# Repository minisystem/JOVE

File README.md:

SYSTEM80 JOVE Multimode Filter
============

Roland Jupiter 6 inspired multimode filter in 14HP Eurorack format. IR3109s replaced with LM13700 OTAs.
Selectable 24 dB low pass, bonus 2 pole 12 dB low pass, band pass and high pass modes.

Product page: http://system80.net/product/jove/<br>

Demos:<br>
https://soundcloud.com/system_80/sets/jove-demo<br>
https://soundcloud.com/system_80/sets/jove-mimoid-demo<br>
https://www.youtube.com/watch?v=VFNtQRDSUw4

EDA files generated in KiCad 4.0.2. Schematic library here: https://github.com/minisystem/MyKicadLibraries/blob/master/MySynthParts.lib
KiCad GitHub libraries required as well. :/
Front panel design by Bartek Kawula.<br>
Hardware design by minisystem: info@system80.net

PCB
===
See /Gerbers/JOVE-gerbers-1.6.zip (BCM857BS SOT-363 changed to BCM857BV SOT-666)

BOM
===
Octopart BOM: https://octopart.com/bom-tool/0BVEzM8i<br>
NOTE 1: R66 and R67 can be 0805 10R resistors or PTC fuses (see BOM for part number)<br>
NOTE 2: C1, C11, C28, C29 can be either 10 pF or 22 pF

CALIBRATION
===========
Feed one of the inputs a 10 Vpp ~50 Hz square wave. In 12 dB mode with frequency and resonance knobs both at minimum (fully CCW), adjust VR5 so that the filter is fully closed. This is best done by ear using headphones. Then switch to HP mode with frequency knob at max (fully CW) and listen to ensure most of the high frequency harmonics are gone. There's a sweet spot where maximum attenuation in both modes can be achieved. The resonance trimmer is used to ensure that there is minimum resonance when the resonance knob is fully CCW. Set the frequency knob at about 12 o'clock and look for a resonance peak on the square wave in 12 dB mode using an oscilloscope. Adjust the input gain so that the output square wave is 10 Vpp. Then use VR7 to to trim away the resonance peak so that the square wave is flat. 

Acknowledgements
================
The idea to hybridize the audio input and control voltage stages from the MKS80 and SH101, respectively, comes directly from
the AMSynths AM8060: http://www.amsynthstore.co.uk/

LICENSE
=======
cc-by-nc-sa
https://creativecommons.org/licenses/by-nc-sa/4.0/<br><br>
Please note the NON-COMMERCIAL (NC) clause of the Creative Commons license.  You do not have permission to build and sell JOVE for monetary compensation.
Make one for yourself, make an extra and sell it to your friend? That's cool. Make several and sell them on eBay/ModularGrid/Tindie? No, don't do that! :)<br><br>
The NC clause isn't going to be around forever and eventually derative works for commercial use will be allowed, but currently commerical use is prohibited by the license. <br><br>
Please also note the ShareAlike (SA) clause of the license: if you create a derivative work, please ensure that it is distributed under the same license and is not used commercially.

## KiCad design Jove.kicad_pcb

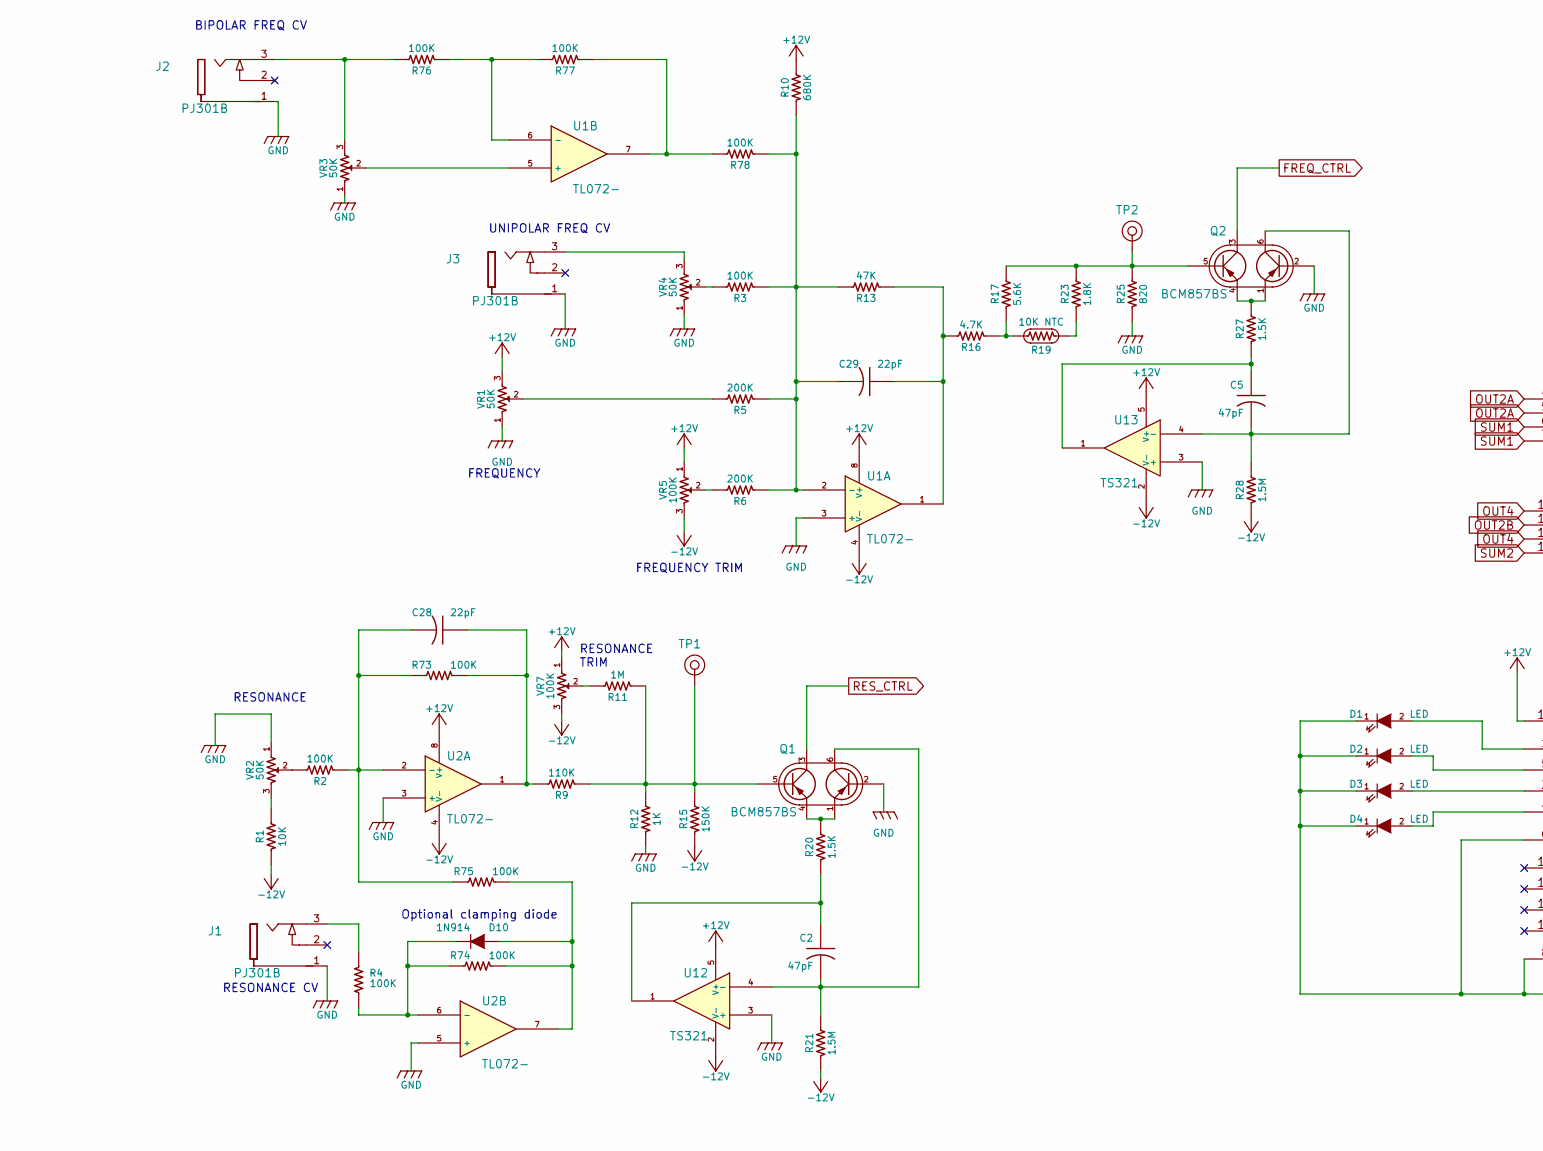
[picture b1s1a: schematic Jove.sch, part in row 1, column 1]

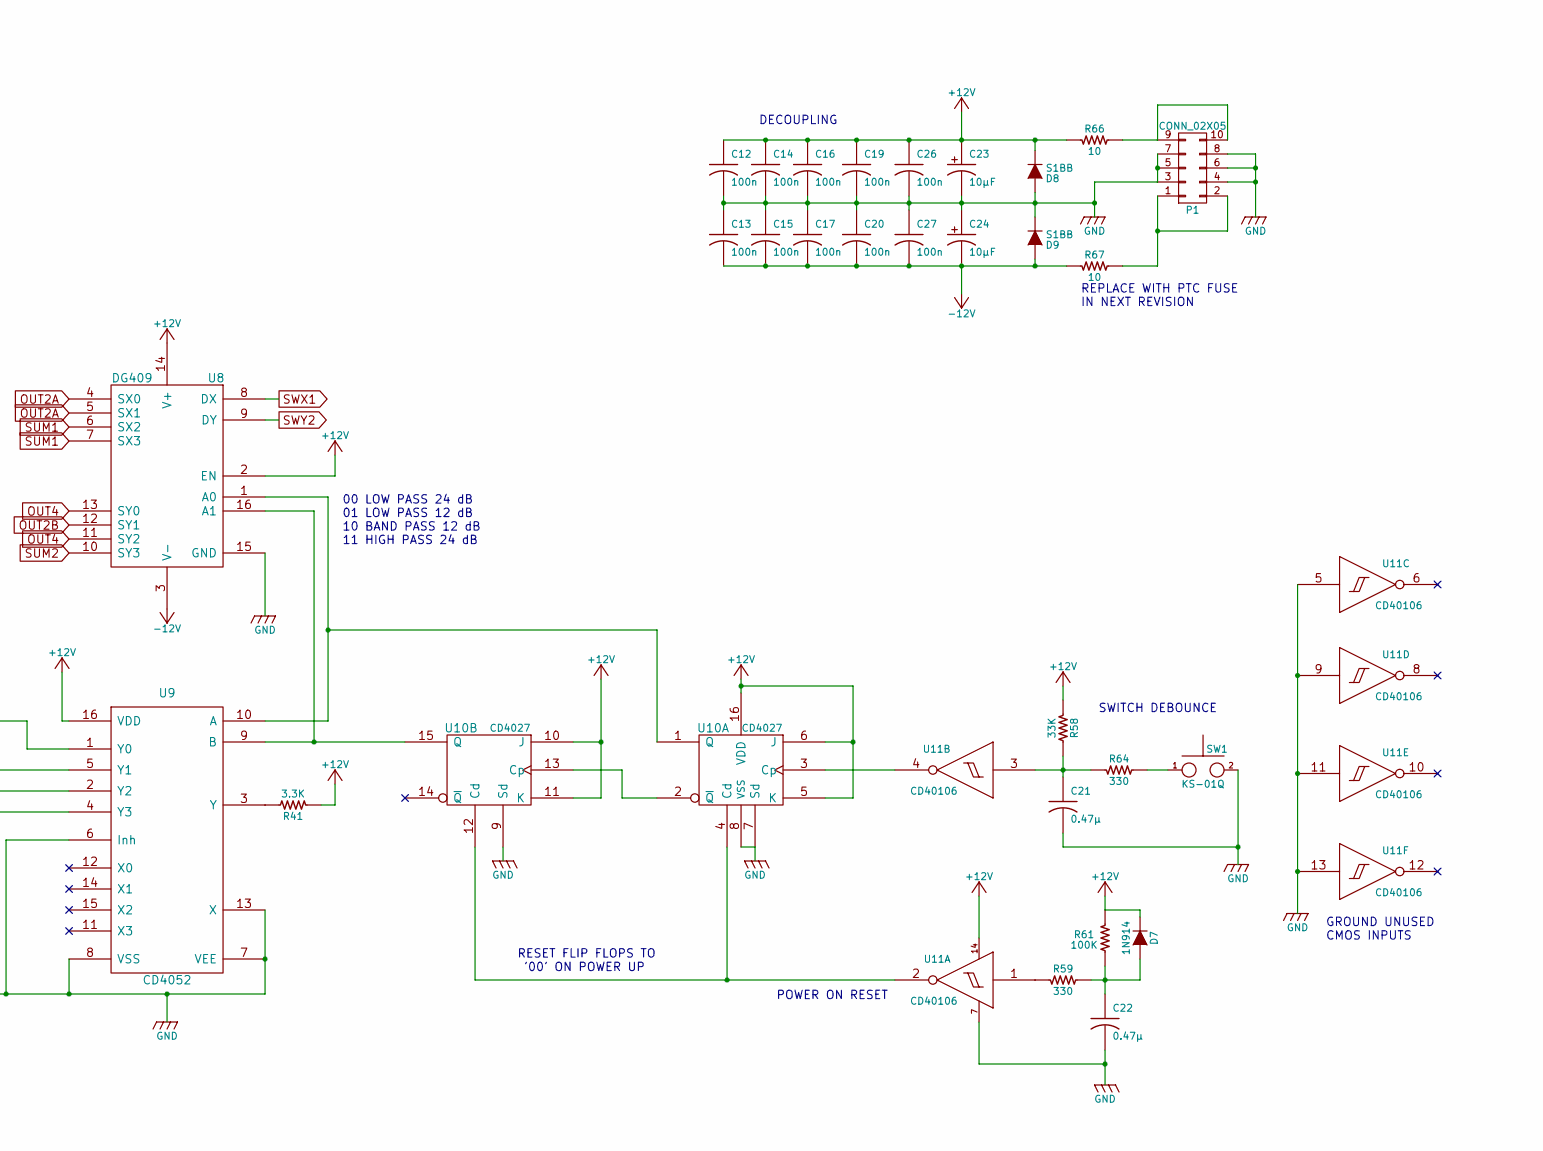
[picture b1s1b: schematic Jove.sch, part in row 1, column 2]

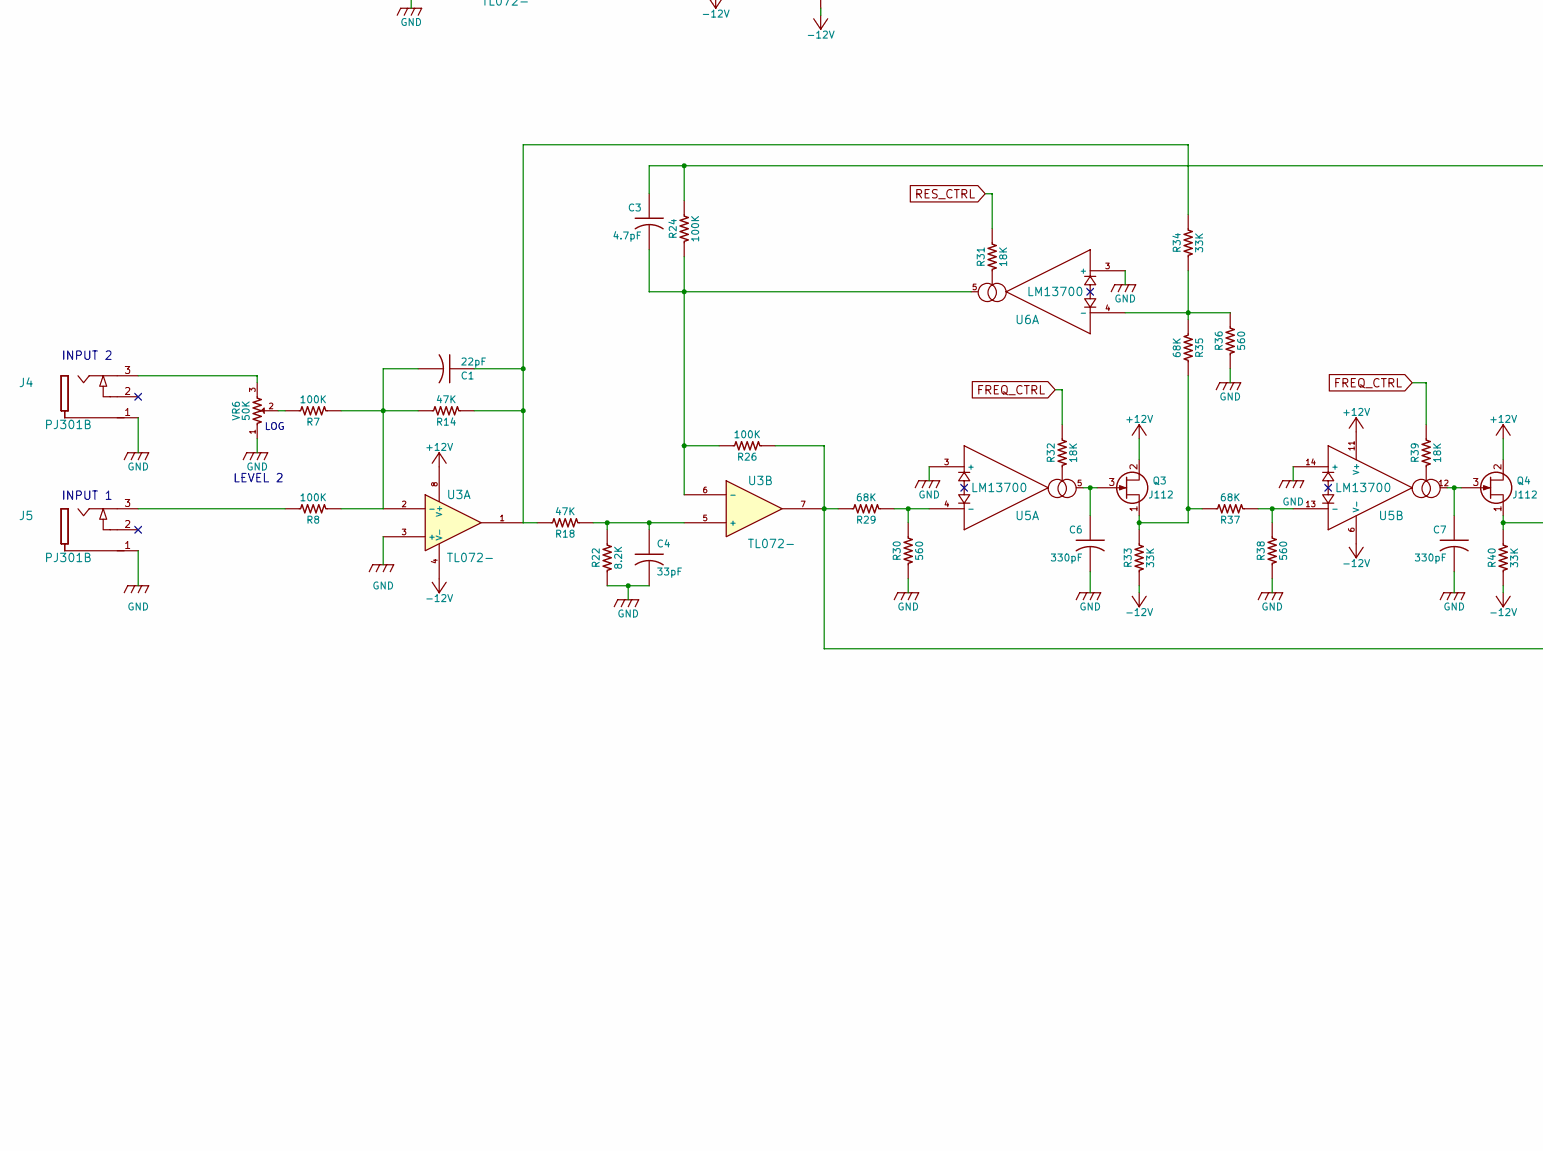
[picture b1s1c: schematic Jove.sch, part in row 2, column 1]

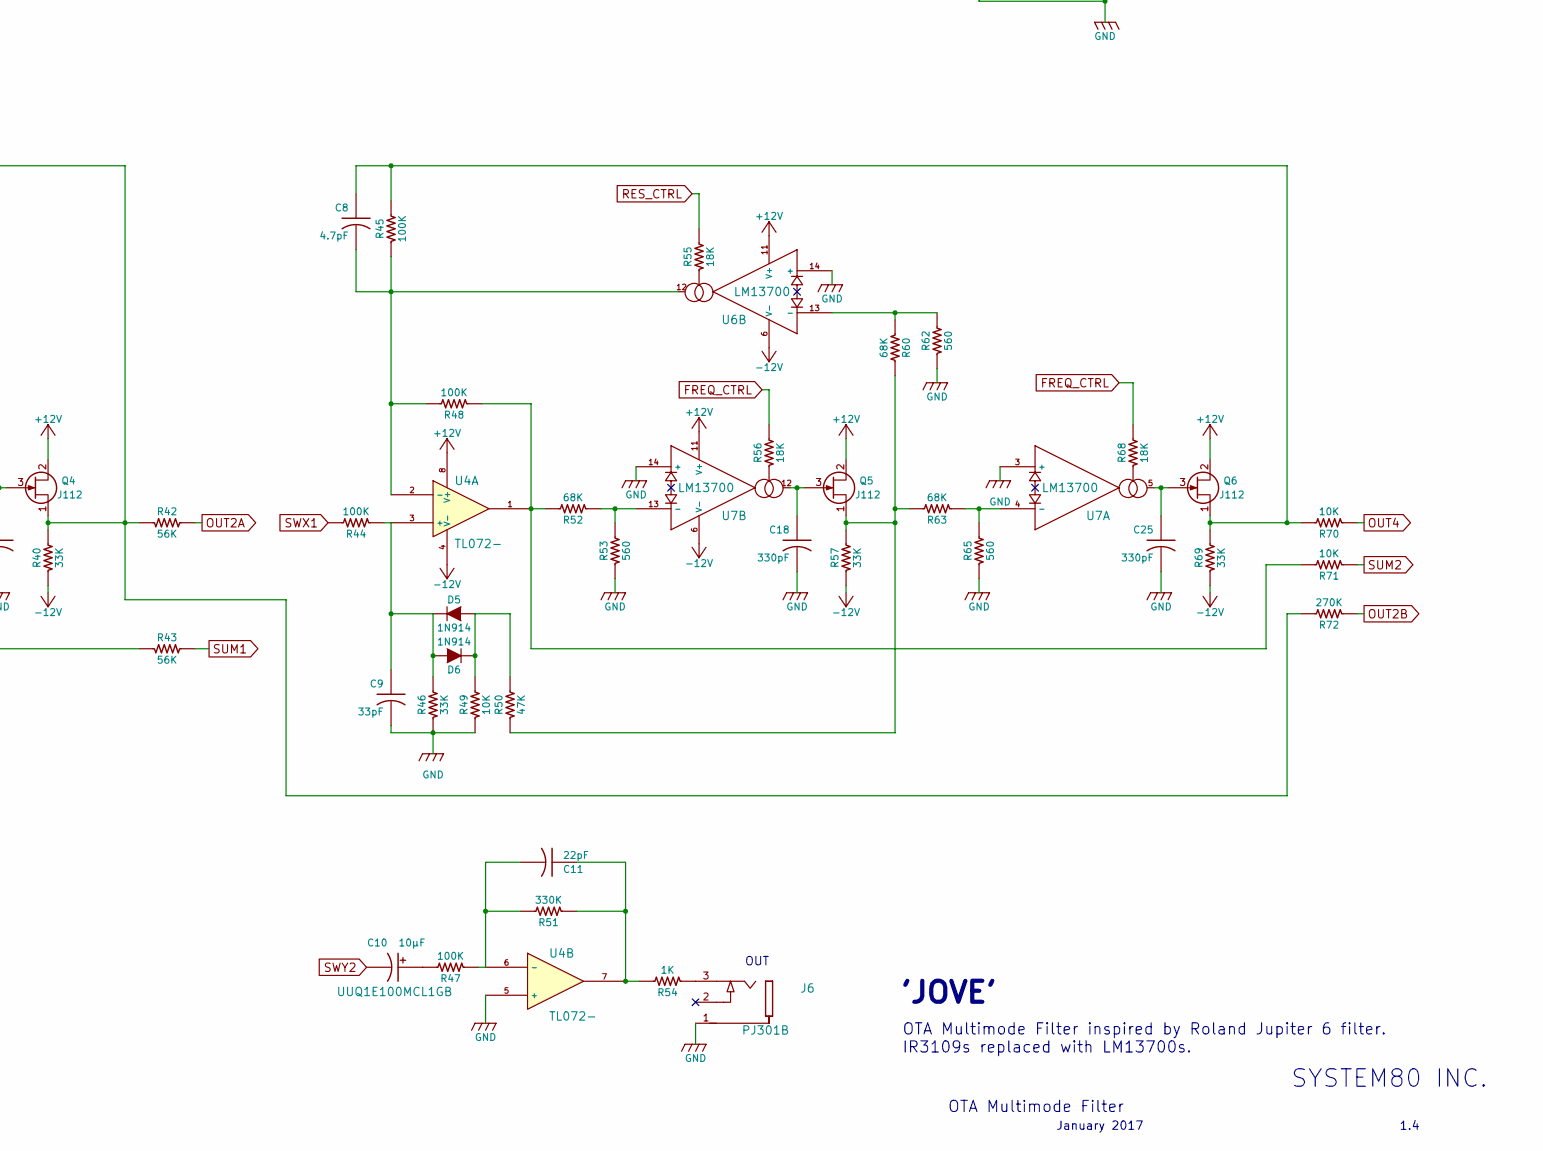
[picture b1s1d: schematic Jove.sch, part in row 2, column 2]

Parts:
C1, C11, C28, C29: 22pF; SM0603-C-JRL
C2, C5: 47pF; SM0603-C-JRL
C3, C8: 4.7pF; SM0603-C-JRL
C4, C9: 33pF; SM0603-C-JRL
C6, C7, C18, C25: 330pF; CAP-BOX-PFR-5MM
C10: 10μF; c_elec_5x5.3; Part Number UUQ1E100MCL1GB
C12, C13, C14, C15, C16, C17, C19, C20, C26, C27: 100n; SM0603-C-JRL
C21, C22: 0.47μ; SM0603-C-JRL
C23, C24: 10μF; c_elec_5x5.3; Part Number UWJ1E100MCL1GB
D1, D2, D3, D4: LED; 3MM-LED-C1A2
D5, D6, D7, D10: 1N914; SOD323-C1A2
D8, D9: S1BB; SMB-1C2A
J1, J2, J3, J4, J5, J6: PJ301B; PJ-301B-JACK-SLOTS
P1: CONN_02X05; Pin_Header_Straight_2x05
Q1, Q2: BCM857BS; sot323-6
Q3, Q4, Q5, Q6: J112; SOT23-JRL
R1, R49, R70, R71: 10K; SM0603-R-JRL
R2, R3, R4, R7, R8, R24, R26, R44, R45, R47, R48, R61, R73, R74, R75, R76, R77, R78: 100K; SM0603-R-JRL
R5, R6: 200K; SM0603-R-JRL
R9: 110K; SM0603-R-JRL
R10: 680K; SM0603-R-JRL
R11: 1M; SM0603-R-JRL
R12, R54: 1K; SM0603-R-JRL
R13, R14, R18, R50: 47K; SM0603-R-JRL
R15: 150K; SM0603-R-JRL
R16: 4.7K; SM0603-R-JRL
R17: 5.6K; SM0603-R-JRL
R19: 10K NTC; SM0805-HAND
R20, R27: 1.5K; SM0603-R-JRL
R21, R28: 1.5M; SM0603-R-JRL
R22: 8.2K; SM0603-R-JRL
R23: 1.8K; SM0603-R-JRL
R25: 820; SM0603-R-JRL
R29, R35, R37, R52, R60, R63: 68K; SM0603-R-JRL
R30, R36, R38, R53, R62, R65: 560; SM0603-R-JRL
R31, R32, R39, R55, R56, R68: 18K; SM0603-R-JRL
R33, R34, R40, R46, R57, R58, R69: 33K; SM0603-R-JRL
R41: 3.3K; SM0603-R-JRL
R42, R43: 56K; SM0603-R-JRL
R51: 330K; SM0603-R-JRL
R59, R64: 330; SM0603-R-JRL
R66, R67: 10; SM0805-HAND
R72: 270K; SM0603-R-JRL
SW1: KS-01Q; KS-01Q-02-JRL
TP1, TP2: TEST_POINT; TEST POINT
U1, U2, U3, U4: TL072-; TSSOP8-JRL
U5, U6, U7: LM13700; SO16-JRL
U8: DG409; SO16-JRL
U9: CD4052; TSSOP-16_4.4x5mm_Pitch0.65mm
U10: CD4027; TSSOP-16_4.4x5mm_Pitch0.65mm
U11: CD40106; TSSOP-14_4.4x5mm_Pitch0.65mm
U12, U13: TS321; SOT-23-5
VR1, VR2, VR3, VR4, VR6: 50K; RV16A-41-JRL
VR5, VR7: 100K; TC33X-2

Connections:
+12V: C12.1, C14.1, C16.1, C19.1, C23.1 (+), C26.1, D7.1 (K), D8.1 (K), Q3.2 (D), Q4.2 (D), Q5.2 (D), Q6.2 (D), R10.2, R41.1, R58.2, R61.2, R66.1, U1.8 (V+), U2.8 (V+), U3.8 (V+), U4.8 (V+), U5.11 (V+), U6.11 (V+), U7.11 (V+), U8.2 (EN), U8.14 (V+), U9.16 (VDD), U10.5 (K), U10.6 (J), U10.10 (J), U10.11 (K), U10.16 (VDD), U11.14 (VDD), U12.5 (V+), U13.5 (V+), VR1.3, VR5.1, VR7.1
-12V: C13.2, C15.2, C17.2, C20.2, C24.2 (-), C27.2, D9.2 (A), R1.2, R15.2, R21.2, R28.2, R33.1, R40.1, R57.1, R67.1, R69.1, U1.4 (V-), U2.4 (V-), U3.4 (V-), U4.4 (V-), U5.6 (V-), U6.6 (V-), U7.6 (V-), U8.3 (V-), U12.2 (V-), U13.2 (V-), VR5.3, VR7.3
FREQ_CTRL: Q2.3 (C2), R32.2, R39.2, R56.2, R68.2
GND: C4.2, C6.2, C7.2, C9.2, C12.2, C13.1, C14.2, C15.1, C16.2, C17.1, C18.2, C19.2, C20.1, C21.2, C22.2, C23.2 (-), C24.1 (+), C25.2, C26.2, C27.1, D1.1 (K), D2.1 (K), D3.1 (K), D4.1 (K), D8.2 (A), D9.1 (K), J1.1, J2.1, J3.1, J4.1, J5.1, J6.1, P1.3, P1.4, P1.5, P1.6, P1.7, P1.8, Q1.2 (B1), Q2.2 (B1), R12.2, R22.1, R25.1, R30.1, R36.1, R38.1, R46.1, R49.1, R53.1, R62.1, R65.1, SW1.2, U1.3 (+), U2.3 (+), U2.5 (+), U3.3 (+), U4.5 (+), U5.3 (+), U5.14 (+), U6.3 (+), U6.14 (+), U7.3 (+), U7.14 (+), U8.15 (GND), U9.6 (Inh), U9.7 (VEE), U9.8 (VSS), U9.13 (X), U10.7 (Sd), U10.8 (VSS), U10.9 (Sd), U11.5 (In), U11.7 (VSS), U11.9 (In), U11.11 (In), U11.13 (In), U12.3 (+), U13.3 (+), VR1.1, VR2.1, VR3.1, VR4.1, VR6.1
unnamed: C1.1, R14.1, R18.2, R34.2, U3.1
unnamed: C1.2, R7.1, R8.1, R14.2, U3.2 (-)
unnamed: C2.1, R20.2, U12.1
unnamed: C2.2, Q1.6 (C1), R21.1, U12.4 (-)
unnamed: C3.1, Q4.1 (S), R24.2, R40.2, R42.2, R72.2
unnamed: C3.2, R24.1, R26.2, U3.6 (-), U6.5
unnamed: C4.1, R18.1, R22.2, U3.5 (+)
unnamed: C5.1, R27.2, U13.1
unnamed: C5.2, Q2.6 (C1), R28.1, U13.4 (-)
unnamed: C6.1, Q3.3 (G), U5.5
unnamed: C7.1, Q4.3 (G), U5.12
unnamed: C8.1, Q6.1 (S), R45.2, R69.2, R70.2
unnamed: C8.2, R45.1, R48.2, U4.2 (-), U6.12
unnamed: C9.1, D5.1 (K), D6.2 (A), R44.1, R46.2, U4.3 (+)
unnamed: C10.1 (+), R47.2
unnamed: C11.1, R51.1, R54.2, U4.7
unnamed: C11.2, R47.1, R51.2, U4.6 (-)
unnamed: C18.1, Q5.3 (G), U7.12
unnamed: C21.1, R58.1, R64.1, U11.3 (In)
unnamed: C22.1, D7.2 (A), R59.2, R61.1
unnamed: C25.1, Q6.3 (G), U7.5
unnamed: C28.1, R9.2, R73.1, U2.1
unnamed: C28.2, R2.1, R73.2, R75.2, U2.2 (-)
unnamed: C29.1, R13.1, R16.2, U1.1
unnamed: C29.2, R3.1, R5.1, R6.1, R10.1, R13.2, R78.1, U1.2 (-)
unnamed: D1.2 (A), U9.1 (Y0)
unnamed: D2.2 (A), U9.5 (Y1)
unnamed: D3.2 (A), U9.2 (Y2)
unnamed: D4.2 (A), U9.4 (Y3)
unnamed: D5.2 (A), D6.1 (K), R49.2, R50.2
unnamed: D10.1 (K), R4.1, R74.2, U2.6 (-)
unnamed: D10.2 (A), R74.1, R75.1, U2.7
unnamed: J1.3, R4.2
unnamed: J2.3, R76.2, VR3.3
unnamed: J3.3, VR4.3
unnamed: J4.3, VR6.3
unnamed: J5.3, R8.2
unnamed: J6.3, R54.1
unnamed: P1.1, P1.2, R67.2
unnamed: P1.9, P1.10, R66.2
unnamed: Q1.1 (E1), Q1.4 (E2), R20.1
unnamed: Q1.5 (B2), R9.1, R11.1, R12.1, R15.1, TP1.1
unnamed: Q2.1 (E1), Q2.4 (E2), R27.1
unnamed: Q2.5 (B2), R17.2, R23.2, R25.2, TP2.1
unnamed: Q3.1 (S), R33.2, R35.2, R37.2
unnamed: Q5.1 (S), R50.1, R57.2, R60.2, R63.2
unnamed: R1.1, VR2.3
unnamed: R2.2, VR2.2
unnamed: R3.2, VR4.2
unnamed: R5.2, VR1.2
unnamed: R6.2, VR5.2
unnamed: R7.2, VR6.2
unnamed: R11.2, VR7.2
unnamed: R16.1, R17.1, R19.2
unnamed: R19.1, R23.1
unnamed: R26.1, R29.2, R43.2, U3.7
unnamed: R29.1, R30.2, U5.4 (-)
unnamed: R31.1, U6.1
unnamed: R32.1, U5.1
unnamed: R34.1, R35.1, R36.2, U6.4 (-)
unnamed: R37.1, R38.2, U5.13 (-)
unnamed: R39.1, U5.16
unnamed: R41.2, U9.3 (Y)
unnamed: R48.1, R52.2, R71.2, U4.1
unnamed: R52.1, R53.2, U7.13 (-)
unnamed: R55.1, U6.16
unnamed: R56.1, U7.16
unnamed: R59.1, U11.1 (In)
unnamed: R60.1, R62.2, U6.13 (-)
unnamed: R63.1, R65.2, U7.4 (-)
unnamed: R64.2, SW1.1
unnamed: R68.1, U7.1
unnamed: R76.1, R77.2, U1.6 (-)
unnamed: R77.1, R78.2, U1.7
unnamed: U1.5 (+), VR3.2
unnamed: U8.1 (A0), U9.10 (A), U10.1 (Q)
unnamed: U10.3 (Cp), U11.4 (Out)
unnamed: U10.4 (Cd), U10.12 (Cd), U11.2 (Out)
unnamed: U10.2 (~Q), U10.13 (Cp)
unnamed: U8.16 (A1), U9.9 (B), U10.15 (Q)
OUT2A: R42.1, U8.4 (SX0), U8.5 (SX1)
OUT2B: R72.1, U8.12 (SY1)
OUT4: R70.1, U8.11 (SY2), U8.13 (SY0)
RES_CTRL: Q1.3 (C2), R31.2, R55.2
SUM1: R43.1, U8.6 (SX2), U8.7 (SX3)
SUM2: R71.1, U8.10 (SY3)
SWX1: R44.2, U8.8 (DX)
SWY2: C10.2 (-), U8.9 (DY)

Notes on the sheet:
00 LOW PASS 24 dB 01 LOW PASS 12 dB 10 BAND PASS 12 dB 11 HIGH PASS 24 dB
POWER ON RESET
SWITCH DEBOUNCE
DECOUPLING
GROUND UNUSED CMOS INPUTS
RESET FLIP FLOPS TO '00' ON POWER UP
LOG
FREQUENCY TRIM
FREQUENCY
RESONANCE
BIPOLAR FREQ CV
RESONANCE CV
RESONANCE TRIM
UNIPOLAR FREQ CV
Optional clamping diode
INPUT 2
LEVEL 2
INPUT 1
OTA Multimode Filter
1.4
OUT
January 2017
OTA Multimode Filter inspired by Roland Jupiter 6 filter. IR3109s replaced with LM13700s.
'JOVE'
SYSTEM80 INC.
REPLACE WITH PTC FUSE IN NEXT REVISION

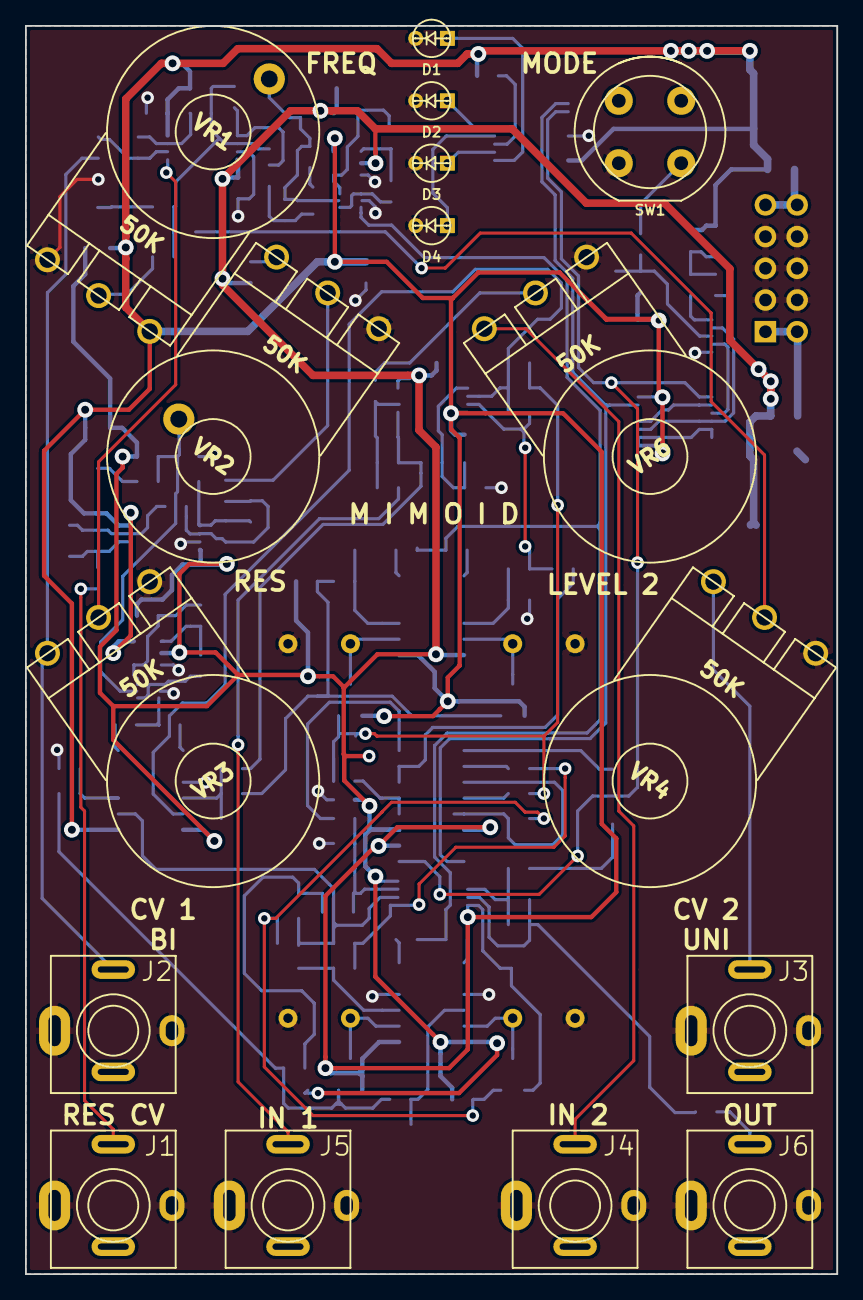
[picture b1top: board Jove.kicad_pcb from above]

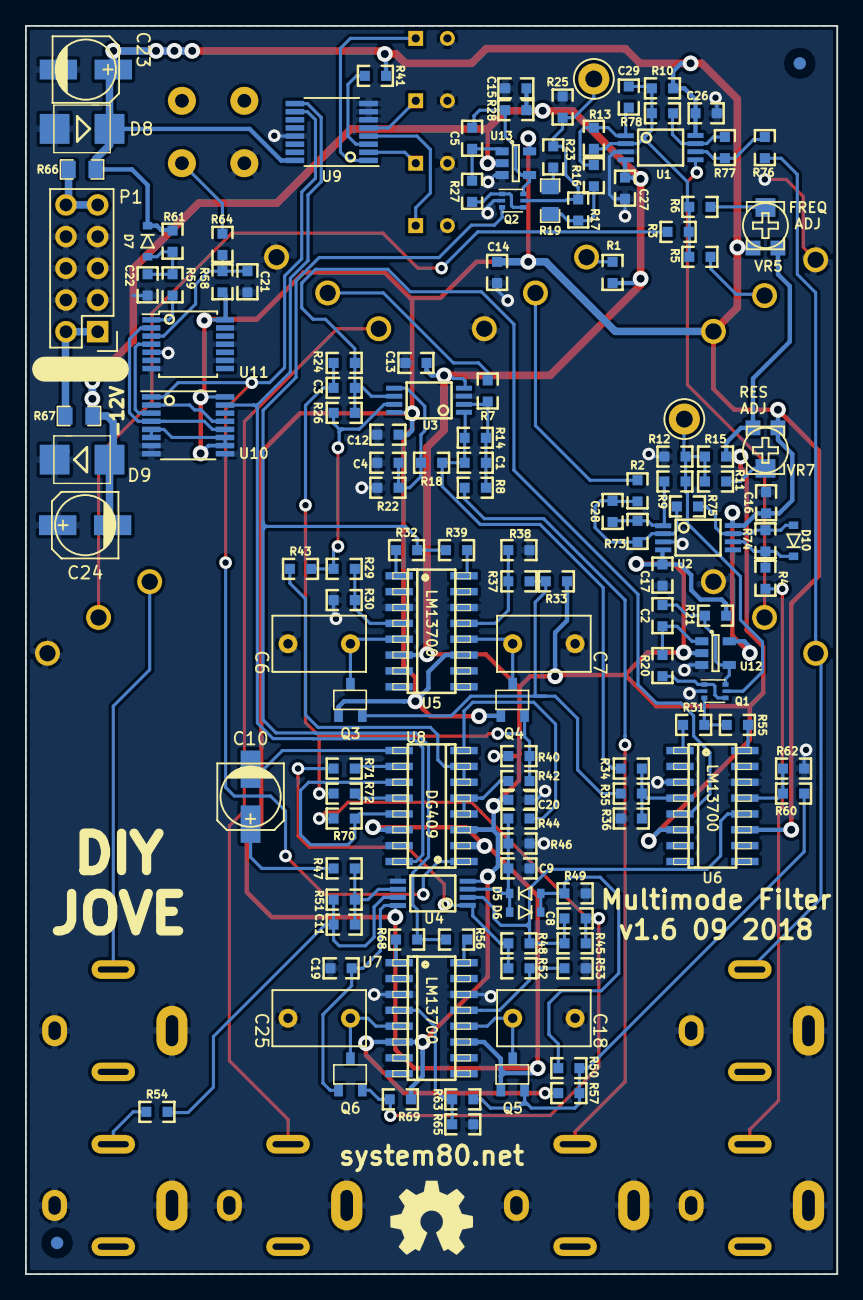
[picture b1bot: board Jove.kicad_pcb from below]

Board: 2 copper layers, 65.0 x 100.0 mm, 153 parts (137 on the bottom side), 92 nets.

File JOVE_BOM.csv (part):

Qty,Line Item,Manufacturer,MPN,Octopart URL,Schematic Reference,Internal Part Number,Description,Total Qty (@ Batch Size: 1),SKU,SKU,Packaging,Packaging,Unit Price (@ Batch Size: 1),Unit Price (@ Batch Size: 1),In Stock,In Stock,MOQ,MOQ,URL,URL,Distributor [Lowest Price (Overall)],SKU [Lowest Price (Overall)],Packaging [Lowest Price (Overall)],Unit Price (@ Batch Size: 1) [Lowest Price (Overall)],Line Total [Lowest Price (Overall)],Batch Total [Lowest Price (Overall)],In Stock [Lowest Price (Overall)],MOQ [Lowest Price (Overall)],URL [Lowest Price (Overall)],Notes
,,,,,,,,,Digi-Key,Mouser,Digi-Key,Mouser,Digi-Key,Mouser,Digi-Key,Mouser,Digi-Key,Mouser,Digi-Key,Mouser,,,,,,,,,,
2,C0603C470J5GACTU,KEMET,C0603C470J5GACTU,https://octopart.com/c0603c470j5gactu-kemet-96565,"C5,C2",47pF,0603,2,399-1056-1-ND,C0603C470J5GACTU,Cut Tape,,0.134505,0.134505,470434,116632,1,,https://octopart.com/click/track?country=CA&ak=68b25f31&sig=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,https://octopart.com/click/track?country=CA&ak=68b25f31&sig=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,Quest,C0603C470J5GACTU,,0.0403515,0.080703,0.080703,106700,,https://octopart.com/click/track?country=CA&ak=68b25f31&sig=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,
4,PFR5331J100J11L4BULK,KEMET,PFR5331J100J11L4BULK,https://octopart.com/pfr5331j100j11l4bulk-kemet-20374205,"C6,C7,C18,C25",330p FILM,5 MM BOX CAP,4,399-7719-ND,PFR5331J100J11L4BULK,Bulk,,0.7666784999999999,0.7666784999999999,629,790,1,,https://octopart.com/click/track?country=CA&ak=68b25f31&sig=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,https://octopart.com/click/track?country=CA&ak=68b25f31&sig=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,Digi-Key,399-7719-ND,Bulk,0.7666784999999999,3.0667139999999997,3.0667139999999997,629,1,https://octopart.com/click/track?country=CA&ak=68b25f31&sig=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,
2,CC0603CRNPO9BN4R7,Yageo,CC0603CRNPO9BN4R7,https://octopart.com/cc0603crnpo9bn4r7-yageo-41162001,"C8,C3",4.7pF,0603,2,311-1740-1-ND,CC0603CRNPO9BN4R7,Cut Tape,,0.134505,0.134505,53904,2742,1,,https://octopart.com/click/track?country=CA&ak=68b25f31&sig=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,https://octopart.com/click/track?country=CA&ak=68b25f31&sig=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,Future Electronics,4871679,Cut Tape,0.0043041600000000005,0.008608320000000001,0.008608320000000001,0,1,https://octopart.com/click/track?c=1&country=CA&ak=68b25f31&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,
2,C0603C330J5GACTU,KEMET,C0603C330J5GACTU,https://octopart.com/c0603c330j5gactu-kemet-87666,"C9,C4",33pF,0603,2,399-1055-1-ND,C0603C330J5GACTU,Cut Tape,,0.134505,0.134505,159937,66424,1,,https://octopart.com/click/track?country=CA&ak=68b25f31&sig=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,https://octopart.com/click/track?country=CA&ak=68b25f31&sig=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,Quest,C0603C330J5GACTU,,0.04438665000000001,0.08877330000000001,0.08877330000000001,87384,,https://octopart.com/click/track?country=CA&ak=68b25f31&sig=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,
1,UUQ1E100MCL1GB,Nichicon,UUQ1E100MCL1GB,https://octopart.com/uuq1e100mcl1gb-nichicon-19038212,C10,10μF,5mm x 5.3mm,1,493-3202-1-ND,UUQ1E100MCL1GB,Cut Tape,,0.6590745,0.6052725000000001,436,1420,1,,https://octopart.com/click/track?country=CA&ak=68b25f31&sig=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,https://octopart.com/click/track?country=CA&ak=68b25f31&sig=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,Arrow,UUQ1E100MCL1GB**MULT1,Cut Tape,0.44184892500000006,0.44184892500000006,0.44184892500000006,190,1,https://octopart.com/click/track?country=CA&ak=68b25f31&sig=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,
4,C0603C100J5GACTU,KEMET,C0603C100J5GACTU,https://octopart.com/c0603c100j5gactu-kemet-138281,"C11,C1,C28,C29",22pF,0603,4,399-1049-1-ND,C0603C100J5GACTU,Cut Tape,,0.134505,0.134505,684636,136314,1,,https://octopart.com/click/track?country=CA&ak=68b25f31&sig=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,https://octopart.com/click/track?country=CA&ak=68b25f31&sig=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,Quest,C0603C100J5GACTU,,0.04438665000000001,0.17754660000000003,0.17754660000000003,90266,,https://octopart.com/click/track?country=CA&ak=68b25f31&sig=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,
2,GRM188R61E105KA12D,Murata,GRM188R61E105KA12D,https://octopart.com/grm188r61e105ka12d-murata-197449,"C22,C21",1μ,0603,2,490-3897-1-ND,GRM188R61E105KA12D,Cut Tape,,0.134505,0.14795550000000002,2332690,474291,1,,https://octopart.com/click/track?country=CA&ak=68b25f31&sig=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,https://octopart.com/click/track?country=CA&ak=68b25f31&sig=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,Arrow,GRM188R61E105KA12D**MULT,,0.058375170000000004,0.11675034000000001,0.11675034000000001,104,1,https://octopart.com/click/track?country=CA&ak=68b25f31&sig=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,
2,EEE-1EA100SR,Panasonic,EEE1EA100SR,https://octopart.com/eee1ea100sr-panasonic-55403445,"C23,C24",10μF,5mm x 5.8mm,2,PCE3894CT-ND,EEE1EA100SR,Cut Tape,,0.44386650000000005,0.48421800000000004,119898,4880,1,,https://octopart.com/click/track?country=CA&ak=68b25f31&sig=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,https://octopart.com/click/track?country=CA&ak=68b25f31&sig=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,Allied Electronics,70257957,Bulk,0.10087875,0.2017575,0.2017575,1445,1,https://octopart.com/click/track?country=CA&ak=68b25f31&sig=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,
10,C0603C104M5RACTU,KEMET,C0603C104M5RACTU,https://octopart.com/c0603c104m5ractu-kemet-11855687,"C27,C20,C19,C17,C16,C15,C14,C13,C12,C26",100n,0603,10,399-7845-1-ND,C0603C104M5RACTU,Cut Tape,,0.039006450000000005,0.021520800000000003,2577395,477739,1,,https://octopart.com/click/track?country=CA&ak=68b25f31&sig=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,https://octopart.com/click/track?country=CA&ak=68b25f31&sig=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,Mouser,C0603C104M5RACTU,,0.021520800000000003,0.21520800000000004,0.21520800000000004,477739,,https://octopart.com/click/track?country=CA&ak=68b25f31&sig=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,
4,WP424SRDT,Kingbright,WP424SRDT,https://octopart.com/wp424srdt-kingbright-5355810,"D1,D2,D3,D4",LED,3 MM LED,4,754-1717-ND,WP424SRDT,Bulk,,0.6590745,0.34971300000000005,9014,1900,1,,https://octopart.com/click/track?country=CA&ak=68b25f31&sig=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,https://octopart.com/click/track?country=CA&ak=68b25f31&sig=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,Mouser,WP424SRDT,,0.34971300000000005,1.3988520000000002,1.3988520000000002,1900,,https://octopart.com/click/track?country=CA&ak=68b25f31&sig=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,
2,S1BB-13-F,Diodes Inc.,S1BB-13-F,https://octopart.com/s1bb-13-f-diodes+inc.-333220,"D8,D9",S1BB,SMB,2,S1BB-FDICT-ND,S1BB-13-F,Cut Tape,,0.4976685,0.564921,32572,4740,1,,https://octopart.com/click/track?country=CA&ak=68b25f31&sig=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,https://octopart.com/click/track?country=CA&ak=68b25f31&sig=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,Freelance Electronics,S1BB-13-F,,0.12105450000000001,0.24210900000000002,0.24210900000000002,3000,,https://octopart.com/click/track?country=CA&ak=68b25f31&sig=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,
4,1N914BWS,Fairchild Semiconductor,1N914BWS,https://octopart.com/1n914bws-fairchild+semiconductor-7850921,"D10,D7,D6,D5",1N914,SOD323,4,1N914BWSCT-ND,1N914BWS,Cut Tape,,0.18830700000000003,0.17485650000000003,253227,61488,1,,https://octopart.com/click/track?country=CA&ak=68b25f31&sig=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,https://octopart.com/click/track?country=CA&ak=68b25f31&sig=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,Rochester Electronics,1N914BWS,,0.026901,0.107604,0.107604,70048,,https://octopart.com/click/track?country=CA&ak=68b25f31&sig=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,
6,PJ301BM,,,,"J1,J2,J3,J4,J5,J6",WQP-PJ301BM,3.5 MM JACK,6,,,,,,,,,,,,,,,,,,,,,,
2,BCM857BS-7-F,Diodes Inc.,BCM857BS-7-F,https://octopart.com/bcm857bs-7-f-diodes+inc.-67250368,"Q2,Q1",BCM857BS,SOT323-6,2,BCM857BS-7-FDICT-ND,BCM857BS-7-F,Cut Tape,,0.44386650000000005,0.403515,950,2760,1,,https://octopart.com/click/track?country=CA&ak=68b25f31&sig=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,https://octopart.com/click/track?country=CA&ak=68b25f31&sig=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,Mouser,BCM857BS-7-F,,0.403515,0.80703,0.80703,2760,,https://octopart.com/click/track?country=CA&ak=68b25f31&sig=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,
4,MMBFJ112,Fairchild Semiconductor,MMBFJ112,https://octopart.com/mmbfj112-fairchild+semiconductor-13412317,"Q6,Q5,Q4,Q3",J112,SOT23,4,MMBFJ112CT-ND,,Cut Tape,,0.618723,,14344,,1,,https://octopart.com/click/track?country=CA&ak=68b25f31&sig=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,,Future Electronics,3286895,Cut Tape,0.1129842,0.4519368,0.4519368,0,1,https://octopart.com/click/track?c=1&country=CA&ak=68b25f31&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,
4,RC0603FR-0710KL,Yageo,RC0603FR-0710KL,https://octopart.com/rc0603fr-0710kl-yageo-40025538,"R1,R49,R70,R71",10K,0603,4,311-10.0KHRCT-ND,RC0603FR-0710KL,Cut Tape,,0.134505,0.134505,17944628,1019470,1,,https://octopart.com/click/track?country=CA&ak=68b25f31&sig=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,https://octopart.com/click/track?country=CA&ak=68b25f31&sig=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,Area51,RC0603FR-0710KL,,0.002017575,0.0080703,0.0080703,5385,,https://octopart.com/click/track?country=CA&ak=68b25f31&sig=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,
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
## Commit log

2015-04-27 first commit. Note that this project uses Kicad BZR 5624
2015-04-27 schematic capture almost finished
2015-04-28 schematic capture almost done. Power on Reset circuit breadboarded and implemented in schematic
2015-04-28 capture done, still need to doublecheck and annotate, then do footprint association
2015-04-28 added README.md
2015-04-28 annotation done, export netlist and start footprint assignment
2015-04-29 footprints assigned, about to start layout
2015-04-29 started placing components, pots, jacks, sw1 and LEDs placed
2015-04-30 placing components, a few footprints updated
2015-05-01 components placed, beginning to route. current version crashes when 3D viewer is launched, going to try to open in previous version
2015-05-02 routed most signals, still need to route power and ground
2015-05-03 routing power, swapped units on hex inverter
2015-05-03 still routing
2015-05-03 8 connections left to route
2015-05-03 routed, could still use refining
2015-05-05 finished routing, mostly cleaned upk, parts modelled in 5365
2015-05-05 minor tweaking of positive power bus
2015-05-05 adjusted silkscreen
2015-05-07 done touching up. doublecheck IC pin outs and do footprint check
2015-05-07 gerbers plotted for footprint testing, still need to check digital IC pinouts
2015-05-07 anode cathode diode swap from latest kicad library updates fixed, ground plane tweaking
2015-05-10 PCB ordered from dirtypcbs.com on May 9
2015-07-27 commit before changing JFET buffer resistor error
2015-07-27 JFET buffer 33K R to GND error fixed to -12V
2016-03-08 clean up duplicate versions of Gerbers, add Panel folder for panel fab and screen graphics
2016-03-08 stray .dxf cleanup and update readme and license
2016-03-08 readme update
2016-03-08 plot pdf schematic
2016-03-14 eps for screen printing added
2016-03-16 changed power-on-reset R61 resistor to 100K for more reliable POR
2016-03-29 cleaned up missing schematic libraries, added link in README.md to project specific library
2016-04-29 Power polarity protection diodes added, TSSOP-8 footprints changed to KiCad standard, removal of references to VRML1 models, Gerber plots updated
2016-10-19 changed CV2 intput to attenuverter
2016-10-19 added resonance CV input
2016-10-20 needed to ad inverting stage to resonance jack input so more positive CV = more resonance. Question: is diode clamp required on resonance CV jack input?
2016-10-20 replaced op amp servo in exponetial converters with TS321
2016-10-21 schematic edited, changes simulated. ready to change layout
2016-10-21 annoated additional components and passed ERC
2016-10-21 updated README.md to reference v1.3
2016-10-23 hacking together v1.3 pcb
2016-10-23 v1.3 routed
2016-10-23 routed and DRC passed, silkscreen edited
2016-10-24 fixed cretnious things only a cretin would do
2016-10-24 cleaned up silkscreen a bit. ready to do panel alignment test
2016-10-24 Gerbers generated and checked
2016-10-24 fixed the cretinous error made by a cretin by which TS321 rails were reversed because said cretin can't pay attention to detail. Also added small pF caps in feedback of freq and res CV input stages
2016-11-11 removed centre trimmer, doesn't seem to be required
2016-11-22 generated BOM
2016-11-22 rename project files to Jove
2016-11-22 updated rescue library references to new project name
2016-12-03 commit before making panel branch
2016-12-28 updated 0603 footprints to square pads to please assembler, added logo, tweaked main rail traces
2017-01-04 genereated gerbers for panelization by PCB house
2017-02-16 corrected D6/D7 reference swap on PCB. Started working on manual
2017-02-16 fiddling with manual. Inkscape text formatting bugs buggin me
2017-02-17 still fiddling with JOVE manual
2017-02-17 manual almost done
2017-02-22 more manual tweaking
2017-04-06 changed R51 and R72 values to incrase overall output gain and bring down LP12 output levels to match other modes
2017-05-27 updated BOM, readme, added octopart link
2017-05-27 updated R72 and R51 in BOM
2017-11-15 updated manual, updated jove.pdf schematic to v1.4
2017-11-15 moved -12V trace away from SW1 and power header
2017-12-28 first rohs commit
2018-05-28 updated .gitignore
2018-05-28 updated readme and .gitignore
2018-05-28 updated readme to emphasize NC use
2018-05-28 updated readme.md and .gitignore
2018-09-20 changed BCM857BS SOT-363 to BCM857BV SOT-666
2020-07-25 Update JOVE_BOM.csv
    Correct the quantity of 100k resistors from 19 to 18
2020-07-25 Update JOVE_BOM.csv
    in the BOM the resistors r67, r66 have package size 0805 in the description field and that size fits on the pcb as well.
    the recommended resistor is a panasonic ERJ-8GEYJ100V which has package size 1206 as can be seen in the datasheet here:
    https://www.mouser.de/datasheet/2/315/AOA0000C301-1488782.pdf
    the correct sized resistor would be the panasonic ERJ-6GEYJ100V
    wrong octopart links removed
